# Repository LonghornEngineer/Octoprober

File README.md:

Octoprober
==========

Temperature logger designed to read 8 different K-type thermocouples. Can log data onto a SD card or to a host computer. Uses a character display for settings and viewing data.

Board Files are for Cadsoft Eagle V6.0+

Created by:
Parker Dillmann
The Longhorn Engineer

http://longhornengineer.com/

Disclaimer and licensing information can be found below.
http://longhornengineer.com/diy/disclaimer/

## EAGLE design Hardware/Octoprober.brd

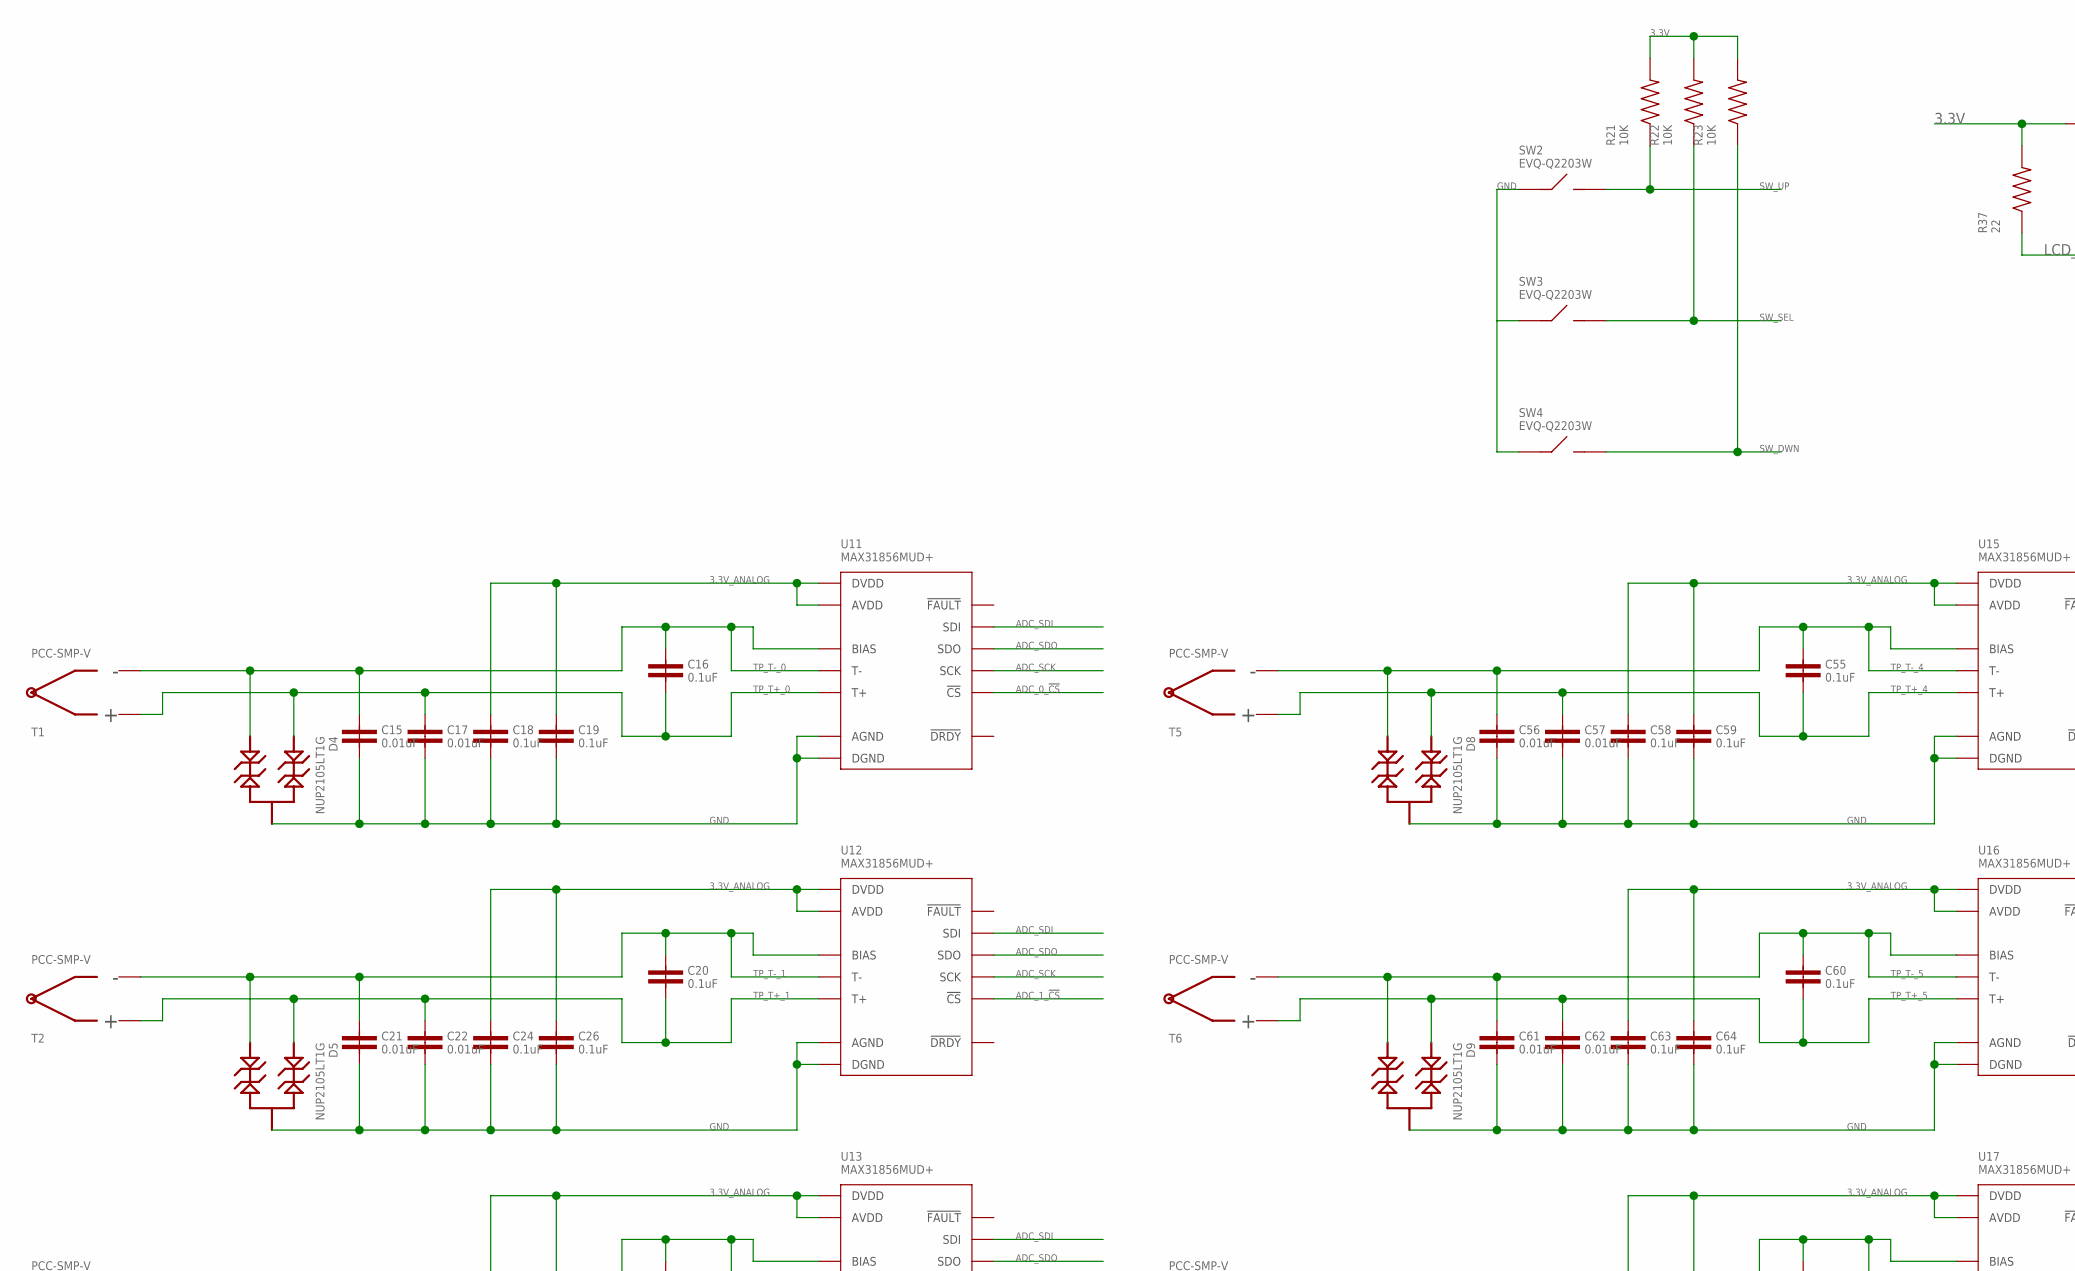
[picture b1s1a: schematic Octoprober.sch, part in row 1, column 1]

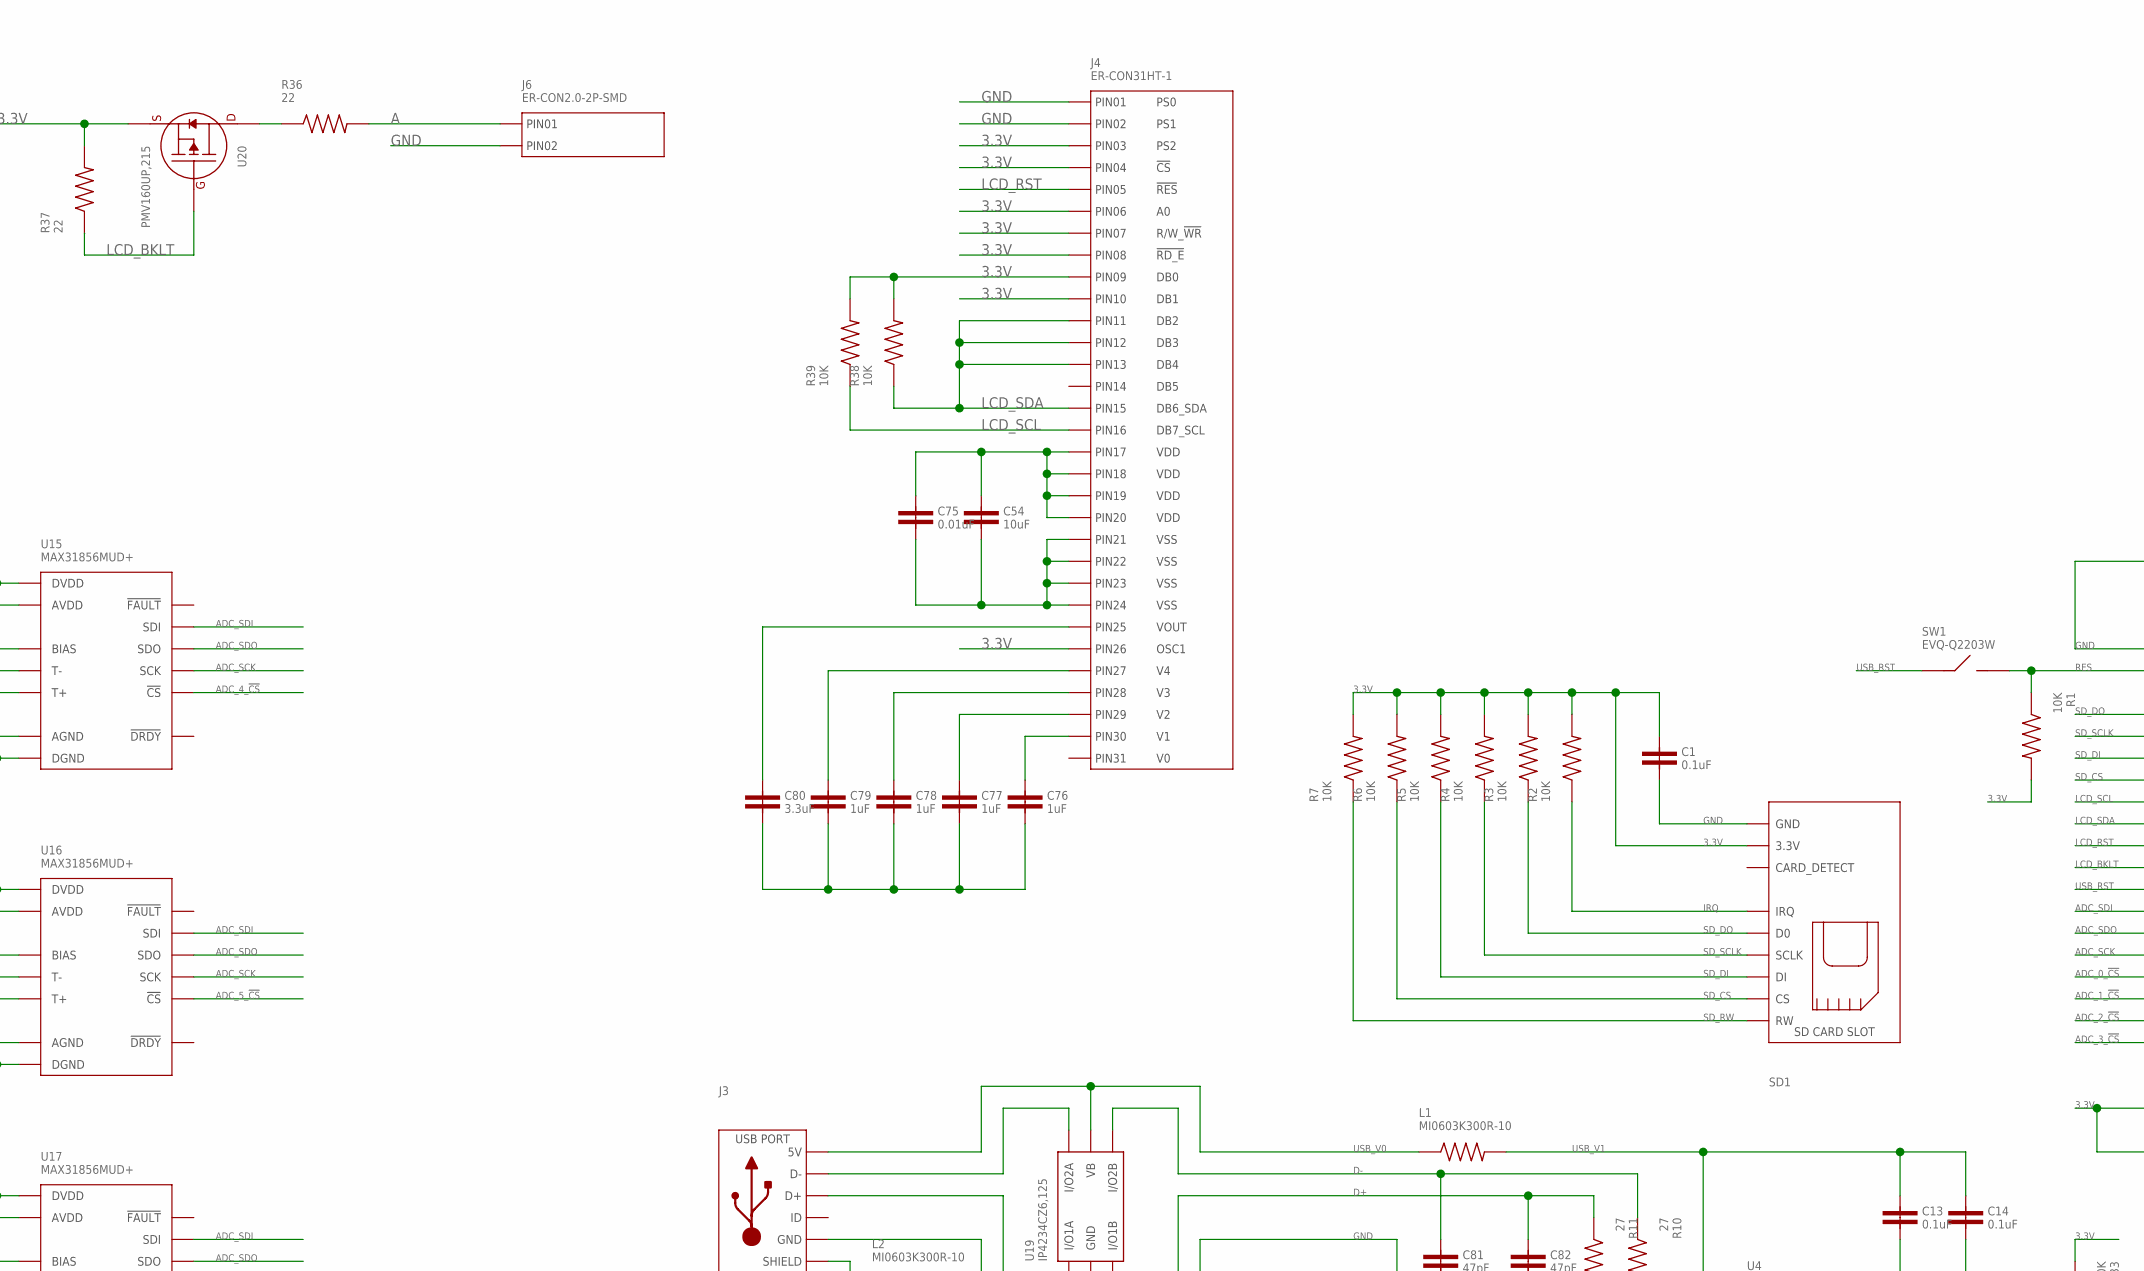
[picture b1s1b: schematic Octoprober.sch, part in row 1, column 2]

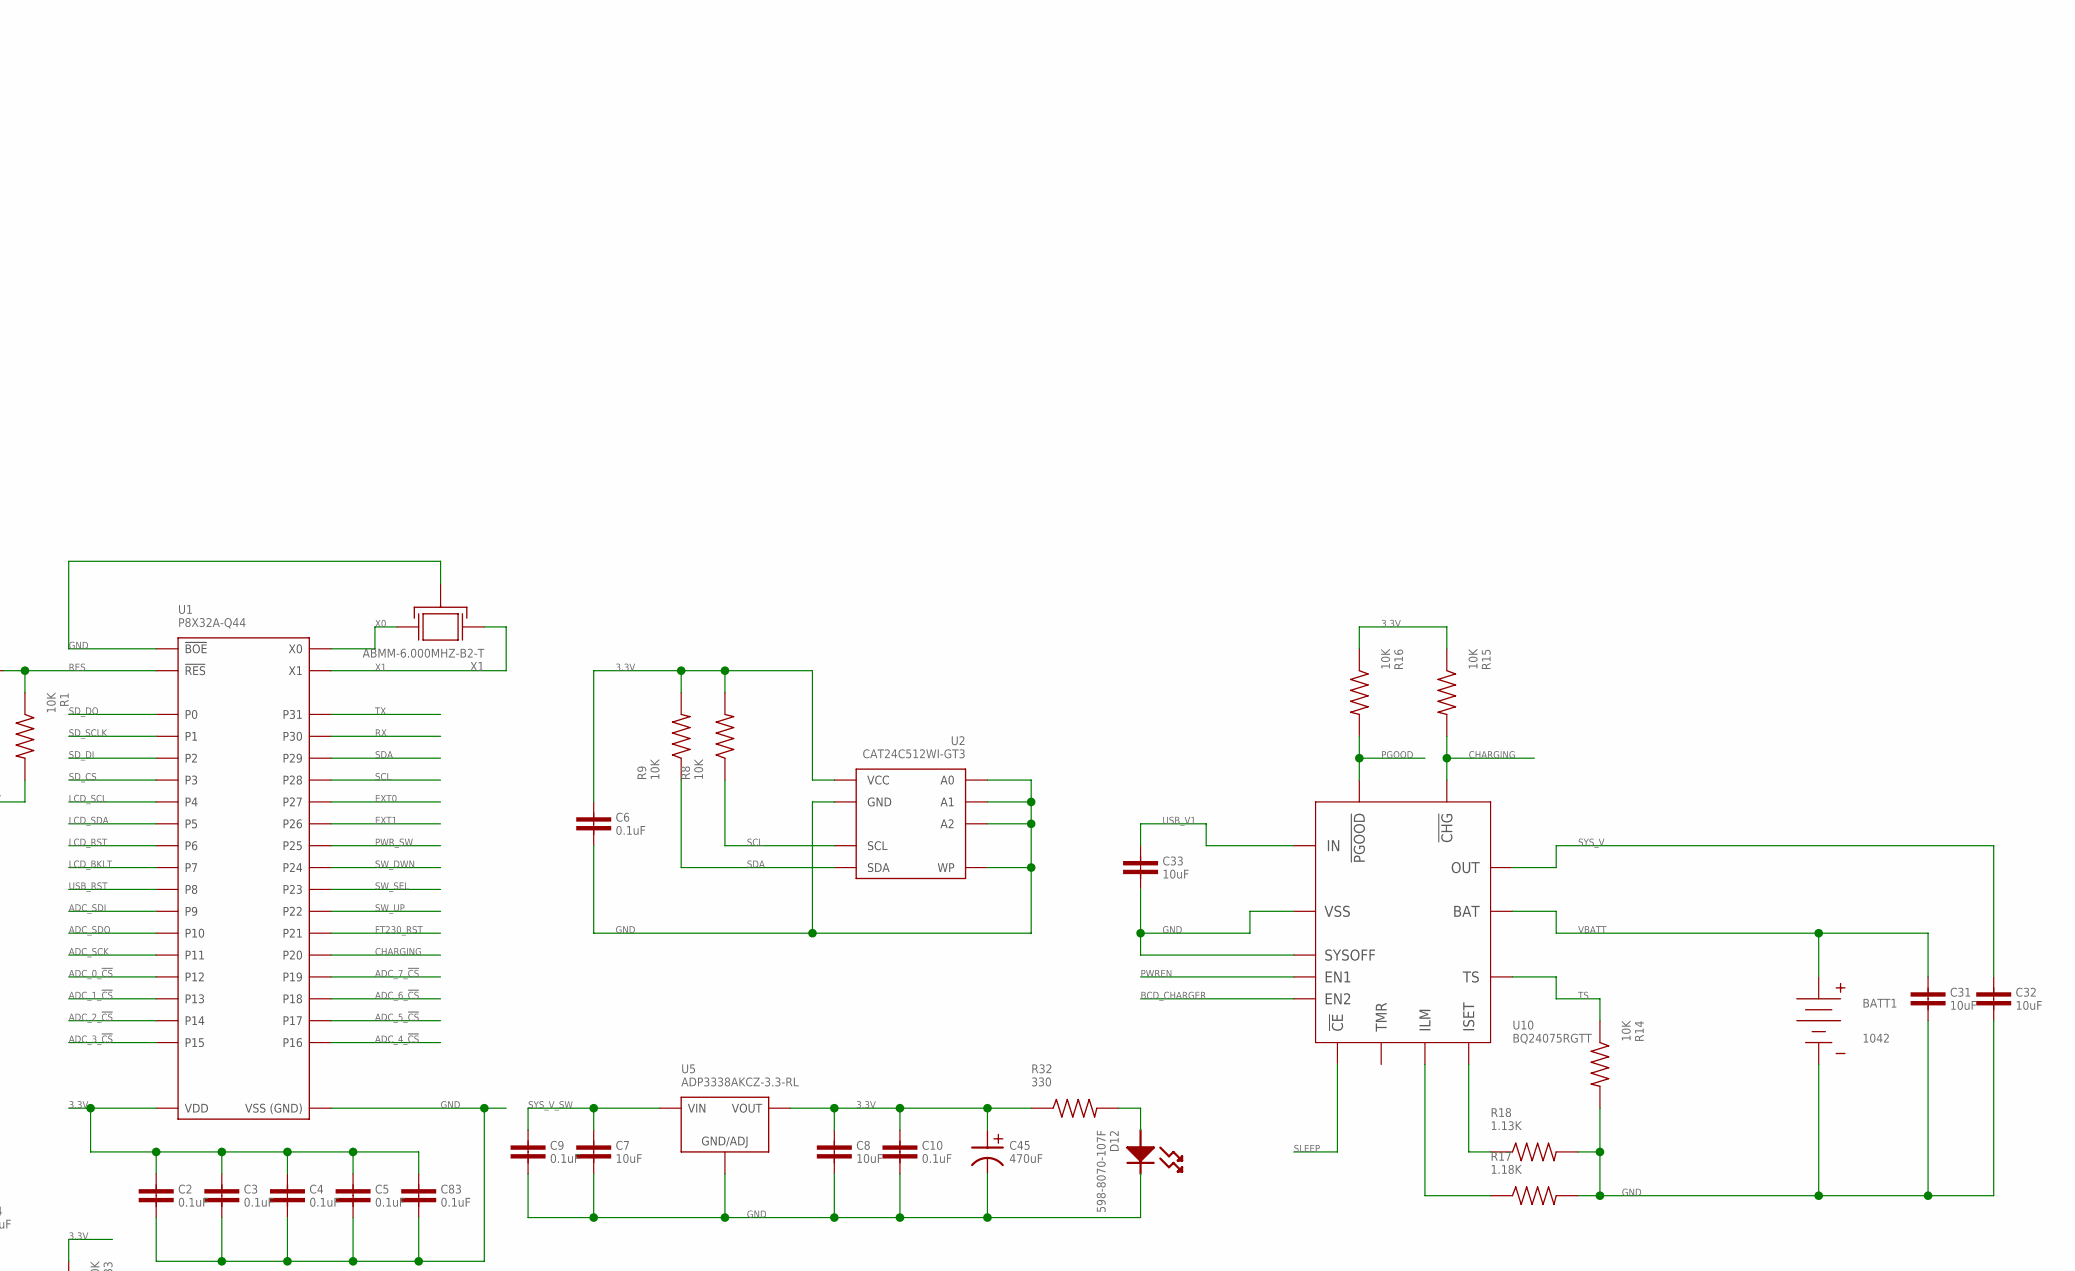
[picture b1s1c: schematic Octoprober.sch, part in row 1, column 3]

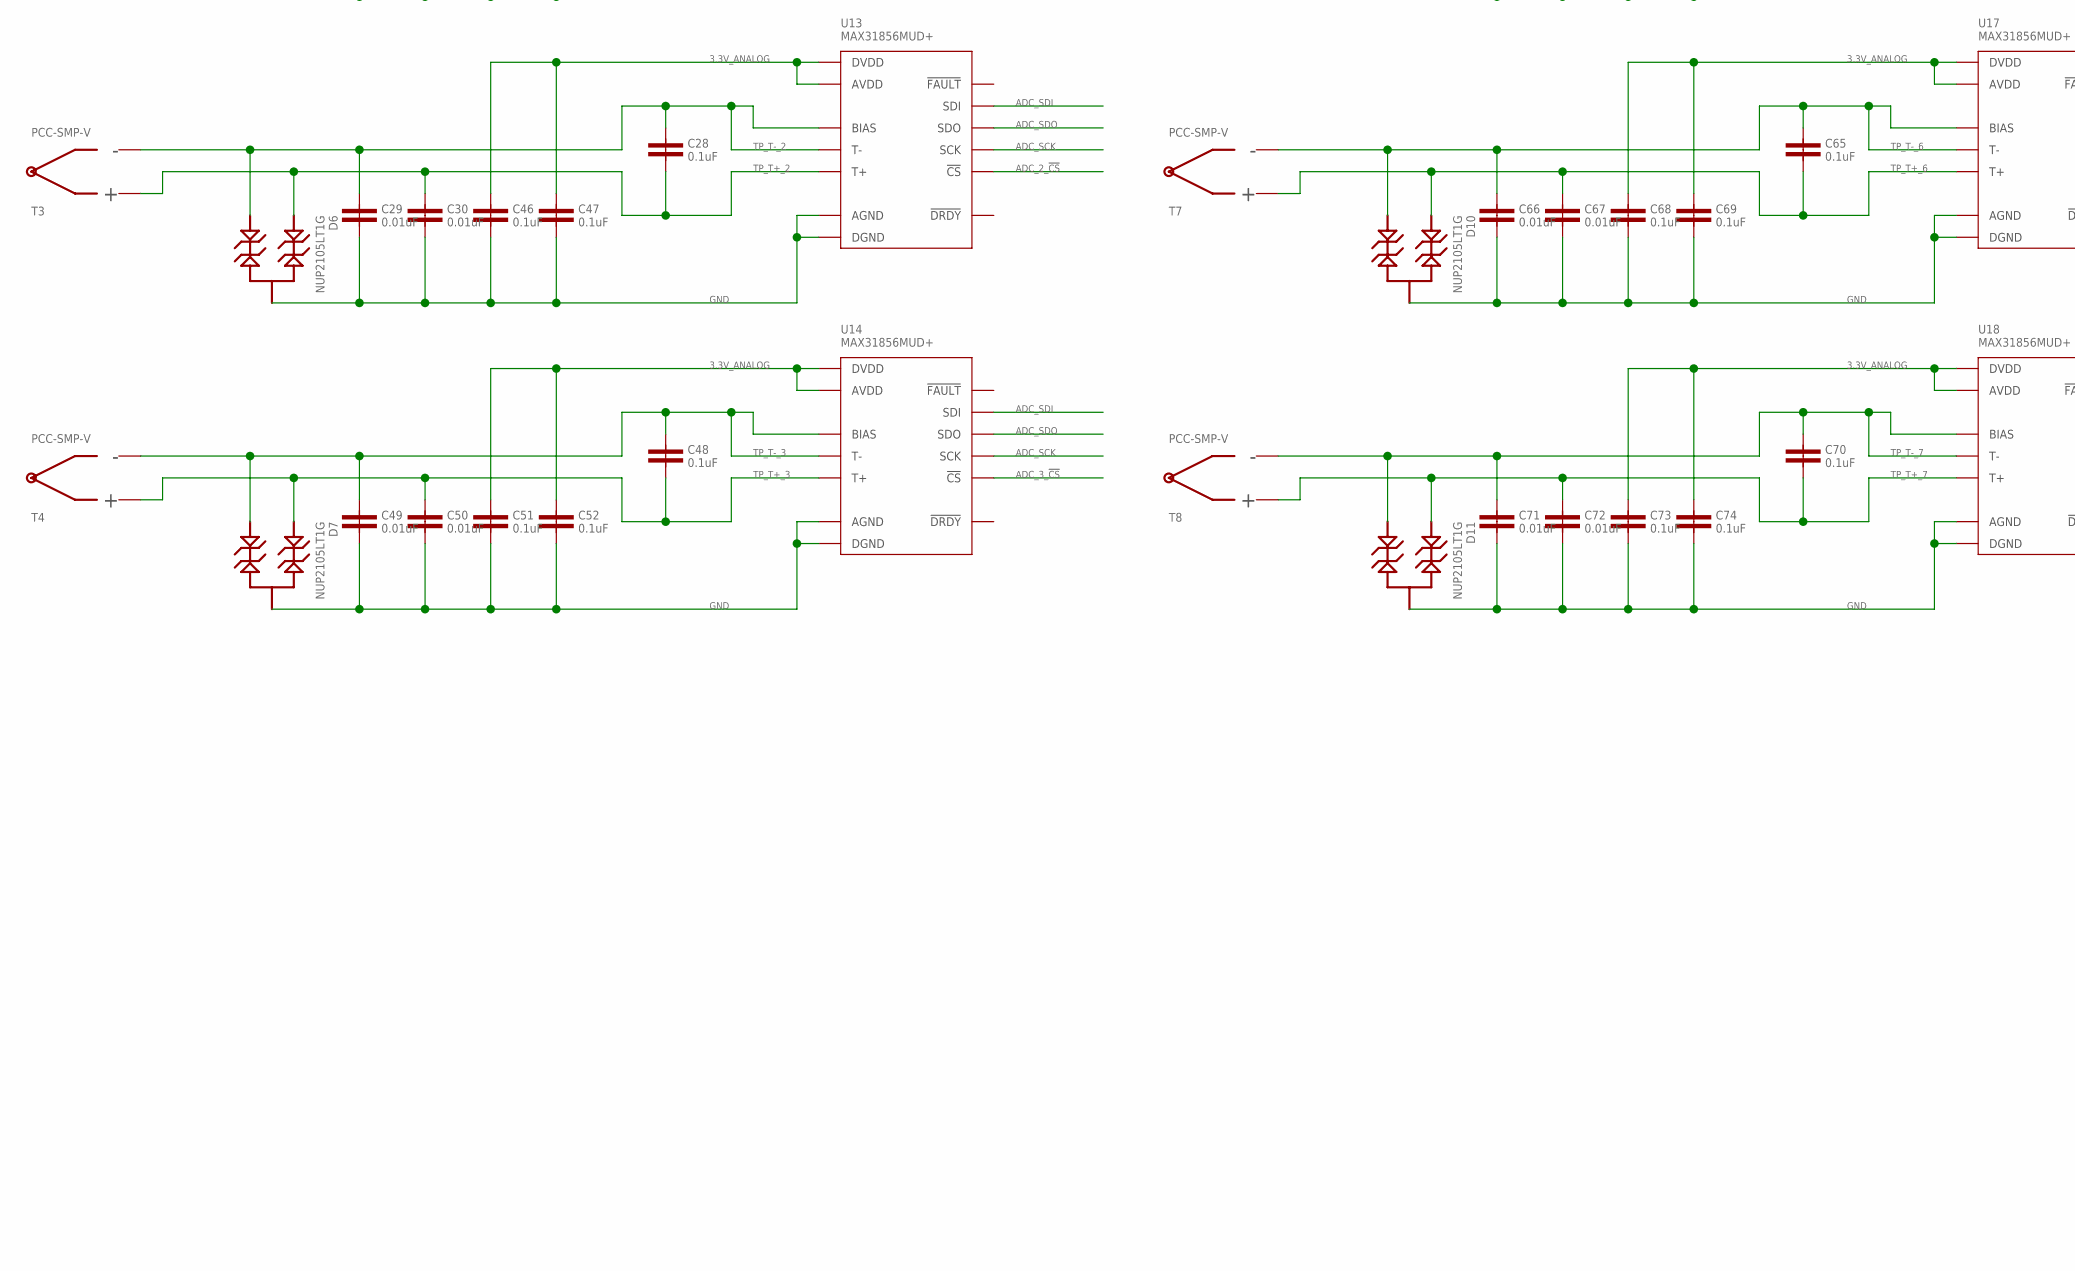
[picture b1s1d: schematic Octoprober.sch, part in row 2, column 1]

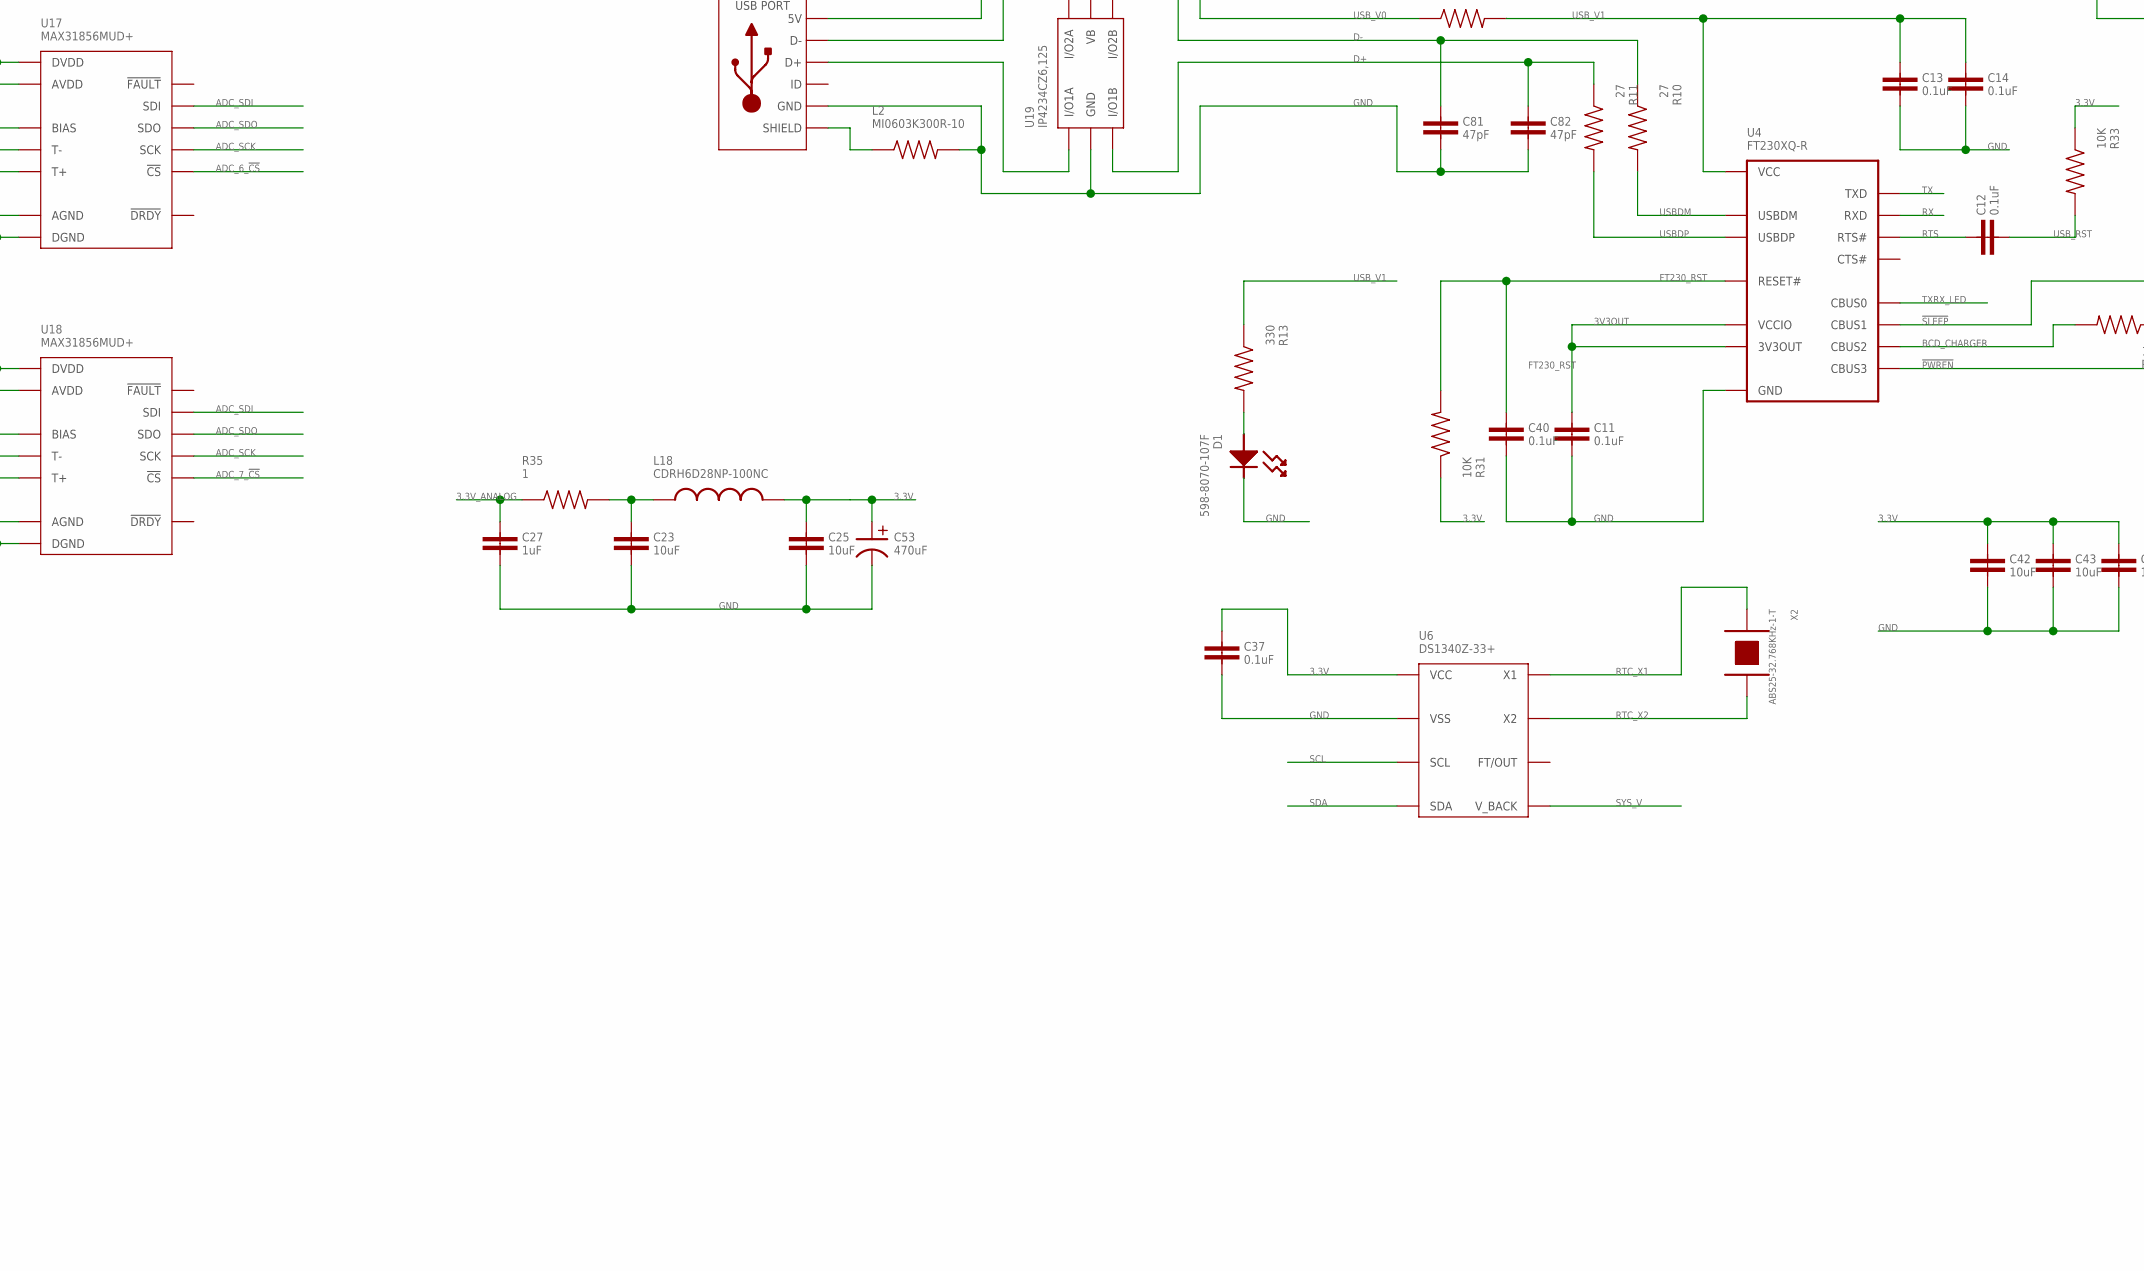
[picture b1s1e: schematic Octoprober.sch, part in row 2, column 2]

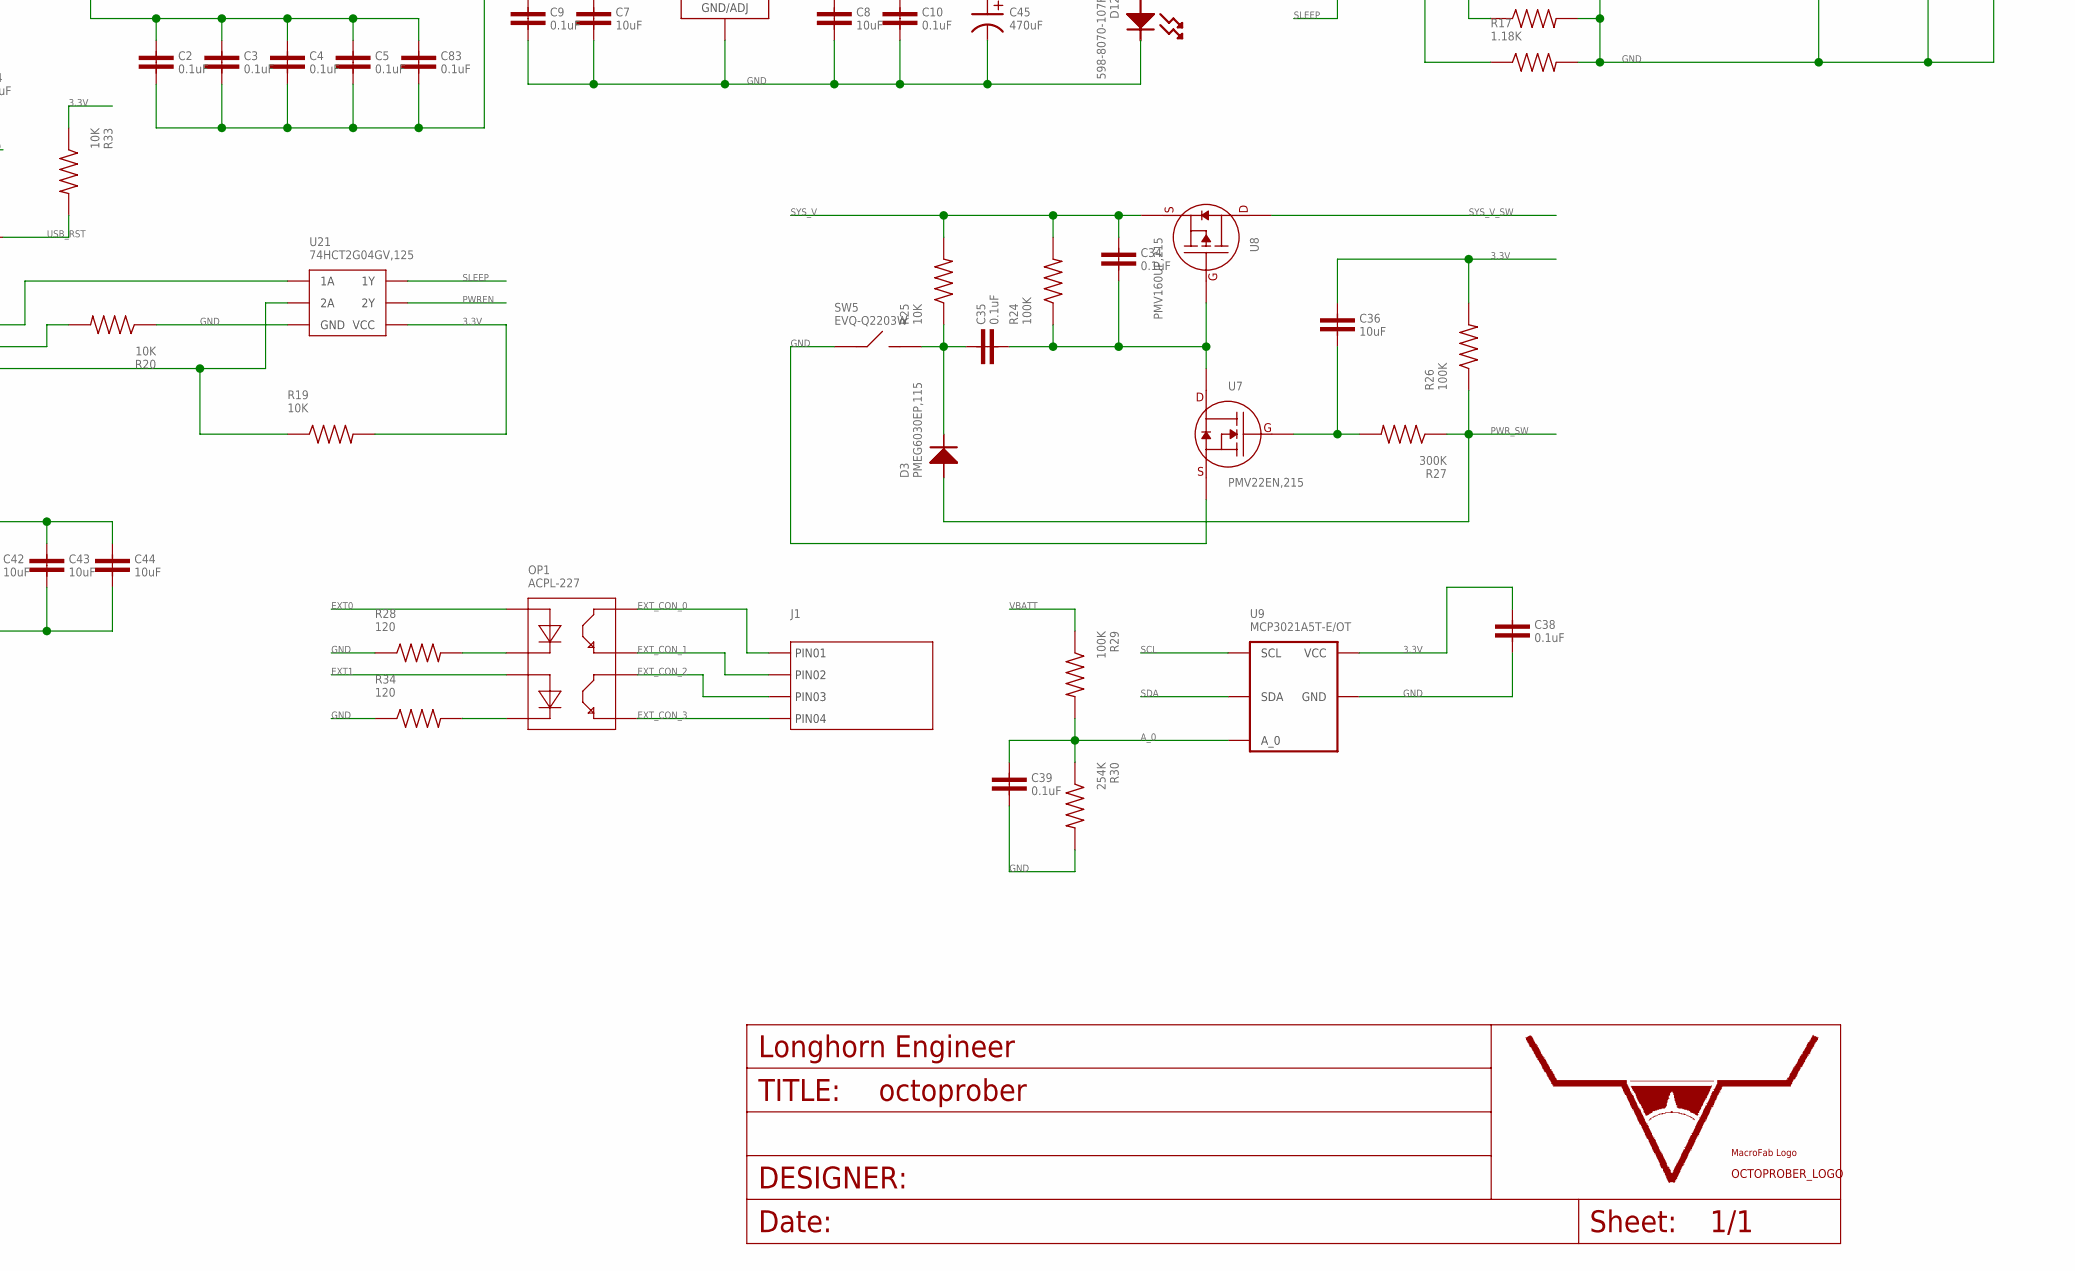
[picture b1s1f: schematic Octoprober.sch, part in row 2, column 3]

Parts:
BATT1: 1042; KEYSTONE_1042
C1, C35: 0.1uF; 0402
C2, C3, C4, C5, C6, C9, C10, C11, C12, C13, C14, C16, C18, C19, C20, C24, C26, C28, C34, C37, C38, C39, C40, C46, C47, C48, C51, C52, C55, C58, C59, C60, C63, C64, C65, C68, C69, C70, C73, C74, C83: 0.1uF; 0603
C7, C8, C23, C25, C31, C32, C33, C36, C42, C43, C44, C54: 10uF; 1206
C15, C17, C21, C22, C29, C30, C49, C50, C56, C57, C61, C62, C66, C67, C71, C72, C75: 0.01uF; 0603
C27, C76, C77, C78, C79: 1uF; 0603
C45, C53: 470uF; CASE_D
C80: 3.3uF; 0603
C81, C82: 47pF; 0603
D1, D12: 598-8070-107F; LED_0805
D3: PMEG6030EP,115; SOD-128
D4, D5, D6, D7, D8, D9, D10, D11: NUP2105LT1G; SOT-23
J1: CON_01X04_2.54MM_PIN_HEADER; 2.54MM_01X04_PIN_HEADER
J3: USB_MICRO_RIGHT; MICROUSB-RIGHT
J4: ER-CON31HT-1
J6: ER-CON2.0-2P-SMD
L1, L2: MI0603K300R-10; 0603
L18: CDRH6D28NP-100NC; CDRH6D28
OP1: ACPL-227; ACPL-227_SO-8
R1, R8, R9, R14, R15, R16, R19, R20, R21, R22, R23, R25, R31, R33, R38, R39: 10K; 0603
R2, R3, R4, R5, R6, R7: 10K; 0402
R10, R11: 27; 0603
R13, R32: 330; 0603
R17: 1.18K; 0603
R18: 1.13K; 0603
R24, R26, R29: 100K; 0603
R27: 300K; 0603
R28, R34: 120; 0603
R30: 254K; 0603
R35: 1; 0603
R36, R37: 22; 0603
SD1: SD_CARD_SLOT_MICRO_RIGHT; MICROSDSLOT-RIGHT
SW1, SW2, SW3, SW4, SW5: EVQ-Q2203W
T1, T2, T3, T4, T5, T6, T7, T8: PCC-SMP-V
U1: P8X32A-Q44; LQFP44
U2: CAT24C512WI-GT3; SOIC-8
U4: FT230XQ-R; FT230X_QFN-16
U5: ADP3338AKCZ-3.3-RL; ADP3338_SOT-223-3
U6: DS1340Z-33+; DS1340Z_SOIC-8
U7: PMV22EN,215; SOT-23-3
U8, U20: PMV160UP,215; SOT-23-3
U9: MCP3021A5T-E/OT; MCP3021_SOT-23-5
U10: BQ24075RGTT; BQ2407X_VQFN-16
U11, U12, U13, U14, U15, U16, U17, U18: MAX31856MUD+; MAX31856_TTSOP-14
U19: IP4234CZ6,125; IP4234CZ6_SOT-457-6
U21: 74HCT2G04GV,125; 74HCT2G04_TTSOP-6
U$1: LHE_FRAME
U$2: OCTOPROBER_LOGONORMAL; OCTOPROBER_LOGO
U$7: MF_LOGOLOGO_MEDIUM; MF_LOGO_MEDIUM
X1: ABMM-6.000MHZ-B2-T; 7MMX5MM
X2: ABS25-32.768KHz-1-T; 8MM_X_3.8MM

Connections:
3.3V: C1.1, C2.1, C3.1, C4.1, C5.1, C6.1, C8.1, C10.1, C25.1, C36.1, C37.1, C38.1, C42.1, C43.1, C44.1, C45.P (POS), C53.P (POS), C83.1, J4.P$3 (PIN3), J4.P$4 (PIN4), J4.P$6 (PIN6), J4.P$7 (PIN7), J4.P$8 (PIN8), J4.P$9 (PIN9), J4.P$10 (PIN10), J4.P$26 (PIN26), L18.P$2, R1.2, R2.2, R3.2, R4.2, R5.2, R6.2, R7.2, R8.2, R9.2, R15.1, R16.1, R19.2, R21.2, R22.2, R23.2, R26.2, R31.1, R32.1, R33.1, R37.2, R38.2, R39.2, SD1.PIN4 (3.3V), U1.8 (VDD), U1.18 (VDD), U1.30 (VDD), U1.40 (VDD), U2.8 (VCC), U5.2 (OUT), U5.PAD (OUT), U6.8 (VCC), U9.1 (VCC), U20.2 (SOURCE), U21.5 (VCC)
3.3V_ANALOG: C18.1, C19.1, C24.1, C26.1, C27.1, C46.1, C47.1, C51.1, C52.1, C58.1, C59.1, C63.1, C64.1, C68.1, C69.1, C73.1, C74.1, R35.1, U11.P$5 (AVDD), U11.P$8 (DVDD), U12.P$5 (AVDD), U12.P$8 (DVDD), U13.P$5 (AVDD), U13.P$8 (DVDD), U14.P$5 (AVDD), U14.P$8 (DVDD), U15.P$5 (AVDD), U15.P$8 (DVDD), U16.P$5 (AVDD), U16.P$8 (DVDD), U17.P$5 (AVDD), U17.P$8 (DVDD), U18.P$5 (AVDD), U18.P$8 (DVDD)
3V3OUT: C11.1, U4.1 (VCCIO), U4.8 (3V3OUT)
!PWREN: R19.1, U4.14 (CBUS3), U21.3 (2A)
!SLEEP: U4.11 (CBUS1), U21.1 (1A)
A: J6.P$1 (PIN1), R36.2
ADC_0_!CS: U1.13 (P12), U11.P$9 (!CS)
ADC_1_!CS: U1.14 (P13), U12.P$9 (!CS)
ADC_2_!CS: U1.15 (P14), U13.P$9 (!CS)
ADC_3_!CS: U1.16 (P15), U14.P$9 (!CS)
ADC_4_!CS: U1.19 (P16), U15.P$9 (!CS)
ADC_5_!CS: U1.20 (P17), U16.P$9 (!CS)
ADC_6_!CS: U1.21 (P18), U17.P$9 (!CS)
ADC_7_!CS: U1.22 (P19), U18.P$9 (!CS)
ADC_SCK: U1.12 (P11), U11.P$10 (SCK), U12.P$10 (SCK), U13.P$10 (SCK), U14.P$10 (SCK), U15.P$10 (SCK), U16.P$10 (SCK), U17.P$10 (SCK), U18.P$10 (SCK)
ADC_SDI: U1.10 (P9), U11.P$12 (SDI), U12.P$12 (SDI), U13.P$12 (SDI), U14.P$12 (SDI), U15.P$12 (SDI), U16.P$12 (SDI), U17.P$12 (SDI), U18.P$12 (SDI)
ADC_SDO: U1.11 (P10), U11.P$11 (SDO), U12.P$11 (SDO), U13.P$11 (SDO), U14.P$11 (SDO), U15.P$11 (SDO), U16.P$11 (SDO), U17.P$11 (SDO), U18.P$11 (SDO)
A_0: C39.1, R29.2, R30.1, U9.3 (A_0)
BCD_CHARGER: R20.2, U4.5 (CBUS2), U10.5 (EN2)
CHARGING: R15.2, U1.23 (P20), U10.9 (!CHG)
D+: C82.1, R11.1, U19.3 (I/O1B)
D-: C81.1, R10.1, U19.4 (I/O2B)
EXT0: OP1.1, U1.34 (P27)
EXT1: OP1.3, U1.33 (P26)
EXT_CON_0: J1.1, OP1.8
EXT_CON_1: J1.2, OP1.7
EXT_CON_2: J1.3, OP1.6
EXT_CON_3: J1.4, OP1.5
FT230_RST: C40.1, R31.2, U1.24 (P21), U4.9 (RESET#)
GND: BATT1.N (-), C1.2, C2.2, C3.2, C4.2, C5.2, C6.2, C7.2, C8.2, C9.2, C10.2, C11.2, C13.2, C14.2, C15.2, C17.2, C18.2, C19.2, C21.2, C22.2, C23.2, C24.2, C25.2, C26.2, C27.2, C29.2, C30.2, C31.2, C32.2, C33.2, C37.2, C38.2, C39.2, C40.2, C42.2, C43.2, C44.2, C45.N (NEG), C46.2, C47.2, C49.2, C50.2, C51.2, C52.2, C53.N (NEG), C56.2, C57.2, C58.2, C59.2, C61.2, C62.2, C63.2, C64.2, C66.2, C67.2, C68.2, C69.2, C71.2, C72.2, C73.2, C74.2, C81.2, C82.2, C83.2, D1.CATHODE, D4.3, D5.3, D6.3, D7.3, D8.3, D9.3, D10.3, D11.3, D12.CATHODE, J3.5 (GND), J4.P$1 (PIN1), J4.P$2 (PIN2), J6.P$2 (PIN2), L2.2, R14.2, R17.2, R18.2, R20.1, R28.1, R30.2, R34.1, SD1.G0 (GND), SD1.G1 (GND), SD1.PIN6 (GND), SW2.1 (A), SW2.2 (A), SW3.1 (A), SW3.2 (A), SW4.1 (A), SW4.2 (A), SW5.1 (A), SW5.2 (A), U1.5 (VSS), U1.6 (BOE'), U1.17 (VSS), U1.27 (VSS), U1.39 (VSS), U2.1 (A0), U2.2 (A1), U2.3 (A2), U2.4 (GND), U2.7 (WP), U4.3 (GND), U4.13 (GND), U4.PAD (GND), U5.1 (GND), U6.4 (VSS), U7.2 (SOURCE), U9.2 (GND), U10.8 (VSS), U10.15 (SYSOFF), U10.PAD0 (VSS), U10.PAD1 (VSS), U11.P$1 (AGND), U11.P$14 (DGND), U12.P$1 (AGND), U12.P$14 (DGND), U13.P$1 (AGND), U13.P$14 (DGND), U14.P$1 (AGND), U14.P$14 (DGND), U15.P$1 (AGND), U15.P$14 (DGND), U16.P$1 (AGND), U16.P$14 (DGND), U17.P$1 (AGND), U17.P$14 (DGND), U18.P$1 (AGND), U18.P$14 (DGND), U19.2 (GND), U21.2 (GND), X1.P$2 (GND), X1.P$4 (GND)
ILM: R17.1, U10.12 (ILM)
IRQ: R2.1, SD1.PIN8 (IRQ)
ISET: R18.1, U10.16 (ISET)
LCD_BKLT: R37.1, U1.4 (P7), U20.1 (GATE)
LCD_RST: J4.P$5 (PIN5), U1.3 (P6)
LCD_SCL: J4.P$16 (PIN16), R39.1, U1.1 (P4)
LCD_SDA: J4.P$11 (PIN11), J4.P$12 (PIN12), J4.P$13 (PIN13), J4.P$15 (PIN15), R38.1, U1.2 (P5)
unnamed: C54.1, C75.1, J4.P$17 (PIN17), J4.P$18 (PIN18), J4.P$19 (PIN19), J4.P$20 (PIN20)
unnamed: D1.ANODE, R13.2
unnamed: C35.1, D3.CATHODE, R25.1, SW5.3 (B), SW5.4 (B)
unnamed: C36.2, R27.2, U7.1 (GATE)
unnamed: OP1.2, R28.2
unnamed: R36.1, U20.3 (DRAIN)
unnamed: C54.2, C75.2, J4.P$21 (PIN21), J4.P$22 (PIN22), J4.P$23 (PIN23), J4.P$24 (PIN24)
unnamed: C80.1, J4.P$25 (PIN25)
unnamed: C79.1, J4.P$27 (PIN27)
unnamed: C78.1, J4.P$28 (PIN28)
unnamed: C77.1, J4.P$29 (PIN29)
unnamed: C76.1, J4.P$30 (PIN30)
unnamed: C76.2, C77.2, C78.2, C79.2, C80.2
unnamed: D12.ANODE, R32.2
unnamed: J3.2 (D-), U19.6 (I/O2A)
unnamed: OP1.4, R34.2
unnamed: C23.1, L18.P$1, R35.2
unnamed: J3.3 (D+), U19.1 (I/O1A)
unnamed: J3.S1 (SLD), J3.S2 (SLD), J3.S3 (SLD), J3.S4 (SLD), J3.S5 (SLD), J3.S6 (SLD), L2.1
PGOOD: R16.2, U10.7 (!PGOOD)
PWREN: U10.6 (EN1), U21.4 (2Y)
PWR_SW: D3.ANODE, R26.1, R27.1, U1.32 (P25)
RES: R1.1, SW1.3 (B), SW1.4 (B), U1.7 (RES')
RTC_X1: U6.1 (X1), X2.1
RTC_X2: U6.2 (X2), X2.4
RTS: C12.1, U4.16 (RTS#)
RX: U1.37 (P30), U4.2 (RXD)
SCL: R8.1, U1.35 (P28), U2.6 (SCL), U6.6 (SCL), U9.5 (SCL)
SDA: R9.1, U1.36 (P29), U2.5 (SDA), U6.5 (SDA), U9.4 (SDA)
SD_CS: R6.1, SD1.PIN2 (CS), U1.44 (P3)
SD_DI: R5.1, SD1.PIN3 (DI), U1.43 (P2)
SD_DO: R3.1, SD1.PIN7 (D0), U1.41 (P0)
SD_RW: R7.1, SD1.PIN1 (RW)
SD_SCLK: R4.1, SD1.PIN5 (SCLK), U1.42 (P1)
SLEEP: U10.4 (!CE), U21.6 (1Y)
SW_DWN: R23.1, SW4.3 (B), SW4.4 (B), U1.31 (P24)
SW_SEL: R22.1, SW3.3 (B), SW3.4 (B), U1.26 (P23)
SW_UP: R21.1, SW2.3 (B), SW2.4 (B), U1.25 (P22)
SYS_V: C32.1, C34.1, R24.2, R25.2, U6.3 (V_BACK), U8.2 (SOURCE), U10.10 (OUT), U10.11 (OUT)
SYS_V_SW: C7.1, C9.1, U5.3 (IN), U8.3 (DRAIN)
S_P_G: C34.2, C35.2, R24.1, U7.3 (DRAIN), U8.1 (GATE)
TP_T+_0: C16.2, C17.1, D4.1, T1.POS, U11.P$4 (T+)
TP_T+_1: C20.2, C22.1, D5.1, T2.POS, U12.P$4 (T+)
TP_T+_2: C28.2, C30.1, D6.1, T3.POS, U13.P$4 (T+)
TP_T+_3: C48.2, C50.1, D7.1, T4.POS, U14.P$4 (T+)
TP_T+_4: C55.2, C57.1, D8.1, T5.POS, U15.P$4 (T+)
TP_T+_5: C60.2, C62.1, D9.1, T6.POS, U16.P$4 (T+)
TP_T+_6: C65.2, C67.1, D10.1, T7.POS, U17.P$4 (T+)
TP_T+_7: C70.2, C72.1, D11.1, T8.POS, U18.P$4 (T+)
TP_T-_0: C15.1, C16.1, D4.2, T1.NEG, U11.P$2 (BIAS), U11.P$3 (T-)
TP_T-_1: C20.1, C21.1, D5.2, T2.NEG, U12.P$2 (BIAS), U12.P$3 (T-)
TP_T-_2: C28.1, C29.1, D6.2, T3.NEG, U13.P$2 (BIAS), U13.P$3 (T-)
TP_T-_3: C48.1, C49.1, D7.2, T4.NEG, U14.P$2 (BIAS), U14.P$3 (T-)
TP_T-_4: C55.1, C56.1, D8.2, T5.NEG, U15.P$2 (BIAS), U15.P$3 (T-)
TP_T-_5: C60.1, C61.1, D9.2, T6.NEG, U16.P$2 (BIAS), U16.P$3 (T-)
TP_T-_6: C65.1, C66.1, D10.2, T7.NEG, U17.P$2 (BIAS), U17.P$3 (T-)
TP_T-_7: C70.1, C71.1, D11.2, T8.NEG, U18.P$2 (BIAS), U18.P$3 (T-)
TS: R14.1, U10.1 (TS)
TX: U1.38 (P31), U4.15 (TXD)
TXRX_LED: U4.12 (CBUS0)
USBDM: R10.2, U4.7 (USBDM)
USBDP: R11.2, U4.6 (USBDP)
USB_RST: C12.2, R33.2, SW1.1 (A), SW1.2 (A), U1.9 (P8)
USB_V0: J3.1 (5V), L1.1, U19.5 (VB)
USB_V1: C13.1, C14.1, C33.1, L1.2, R13.1, U4.10 (VCC), U10.13 (IN)
VBATT: BATT1.P (+), C31.1, R29.1, U10.2 (BAT), U10.3 (BAT)
X0: U1.29 (X0), X1.P$3 (X1)
X1: U1.28 (X1), X1.P$1 (X0)

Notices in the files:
parts and their libraries:
PP_Aesthetics: (c) 2016 Longhorn Engineer
PP_Aesthetics: (c) 2014 Longhorn Engineer
